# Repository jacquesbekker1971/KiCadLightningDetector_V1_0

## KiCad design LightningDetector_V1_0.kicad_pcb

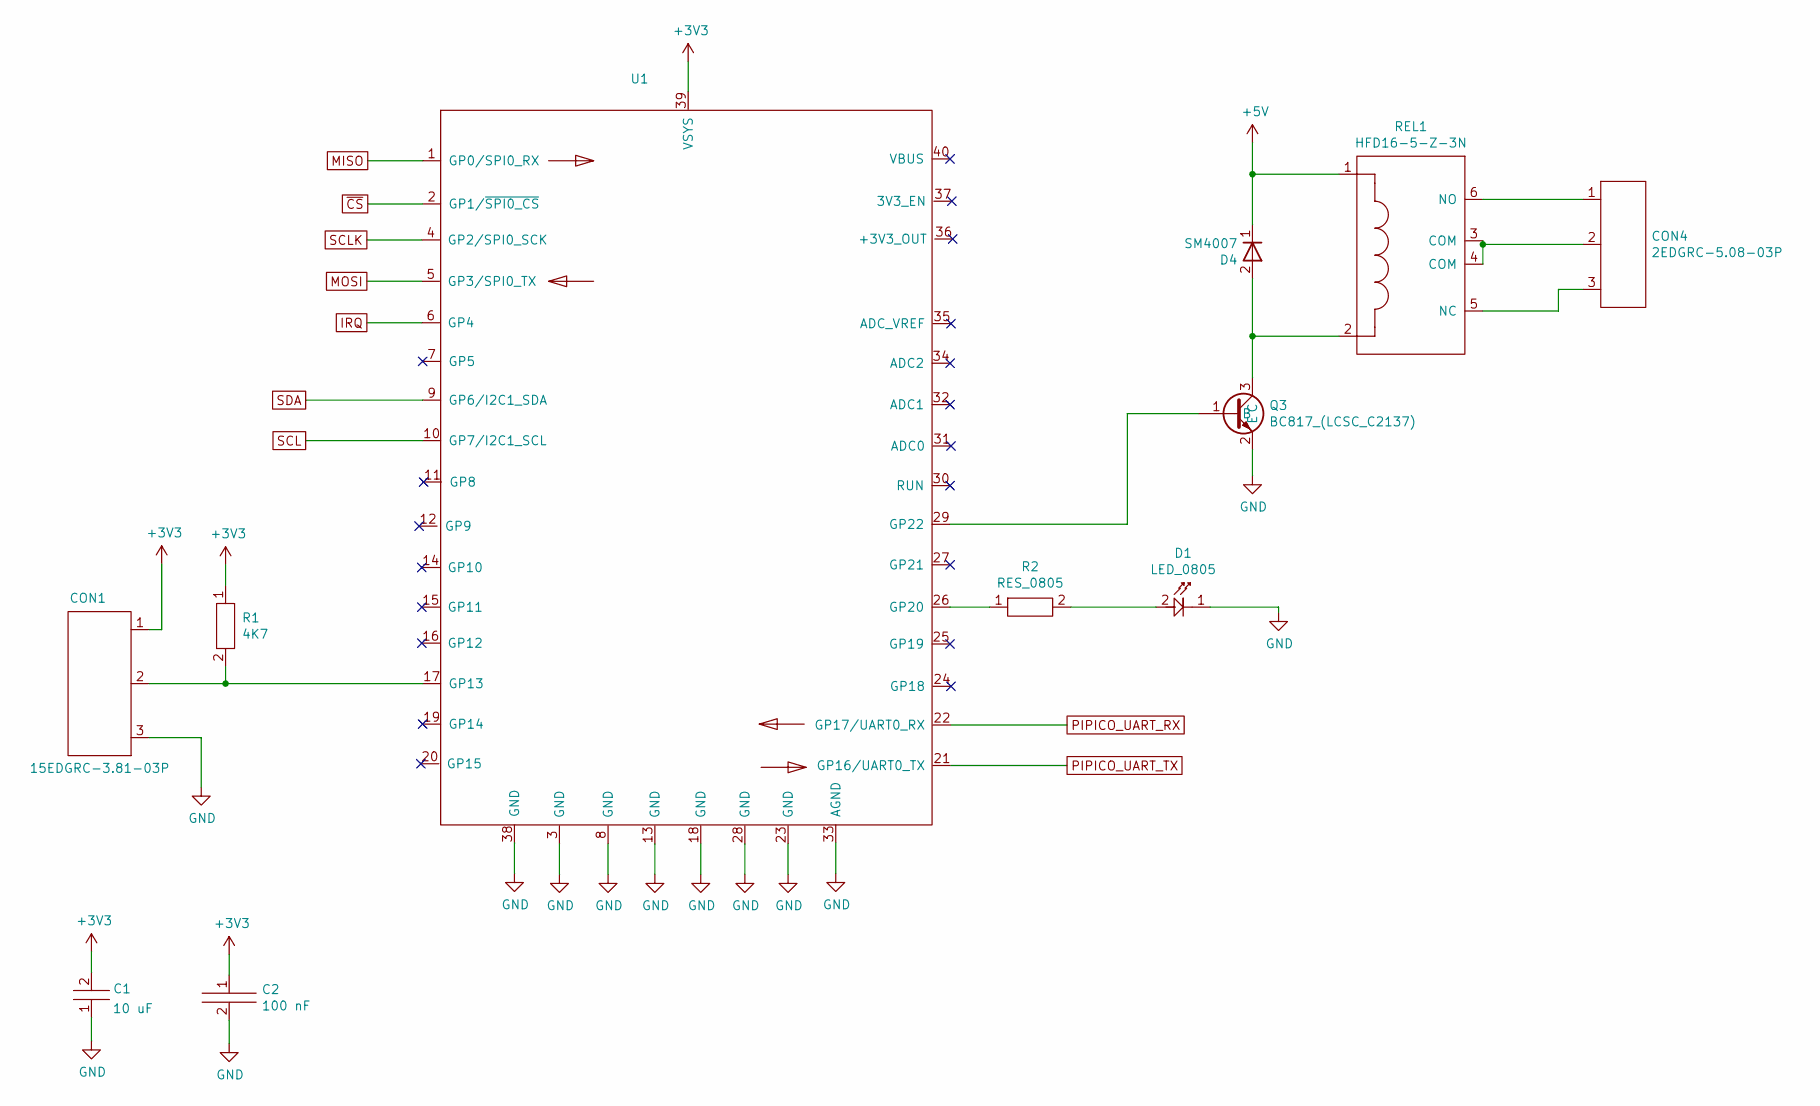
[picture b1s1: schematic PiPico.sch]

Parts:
C1: 10 uF; 1206
C2: 100 nF; C_0805_2012Metric_Pad1.18x1.45mm_HandSolder
CON1: 15EDGRC-3.81-03P
CON4: 2EDGRC-5.08-03P
D1: LED_0805
D4: SM4007; DO-213AB
Q3: BC817_(LCSC_C2137); SOT_23
R1: 4K7; R_0805_2012Metric_Pad1.20x1.40mm_HandSolder
R2: RES_0805; R_0805_2012Metric_Pad1.20x1.40mm_HandSolder
REL1: HFD16-5-Z-3N
U1: PiPico

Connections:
+5V: D4.1, REL1.1; also elsewhere on the board
GND: C1.1, C2.2, CON1.3, D1.1, Q3.2 (E), U1.3 (GND), U1.8 (GND), U1.13 (GND), U1.18 (GND), U1.23 (GND), U1.28 (GND), U1.33 (AGND), U1.38 (GND); also elsewhere on the board
IRQ: U1.6 (GP4); also elsewhere on the board
MISO: U1.1 (GP0/SPI0_RX); also elsewhere on the board
MOSI: U1.5 (GP3/SPI0_TX); also elsewhere on the board
unnamed: CON1.2, R1.2, U1.17 (GP13)
unnamed: CON4.1, REL1.6 (NO)
unnamed: CON4.2, REL1.3 (COM), REL1.4 (COM)
unnamed: CON4.3, REL1.5 (NC)
unnamed: D1.2, R2.2
unnamed: D4.2, Q3.3 (C), REL1.2
unnamed: Q3.1 (B), U1.29 (GP22)
unnamed: R2.1, U1.26 (GP20)
PIPICO_UART_RX: U1.22 (GP17/UART0_RX); also elsewhere on the board
PIPICO_UART_TX: U1.21 (GP16/UART0_TX); also elsewhere on the board
SCL: U1.10 (GP7/I2C1_SCL); also elsewhere on the board
SCLK: U1.4 (GP2/SPI0_SCK); also elsewhere on the board
SDA: U1.9 (GP6/I2C1_SDA); also elsewhere on the board
~CS: U1.2 (GP1/~SPI0_CS); also elsewhere on the board

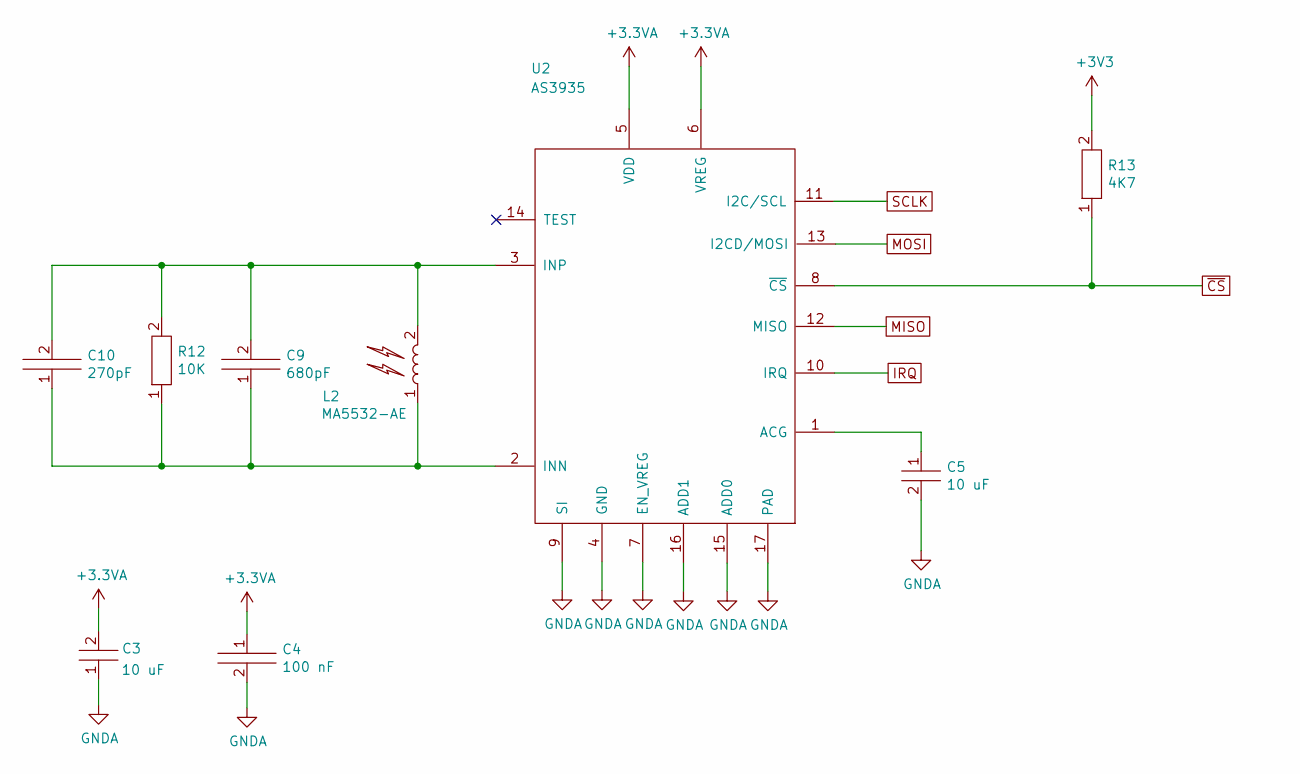
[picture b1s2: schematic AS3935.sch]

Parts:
C3, C5: 10 uF; 1206
C4: 100 nF; C_0805_2012Metric_Pad1.18x1.45mm_HandSolder
C9: 680pF; C_0805_2012Metric_Pad1.18x1.45mm_HandSolder
C10: 270pF; C_0805_2012Metric_Pad1.18x1.45mm_HandSolder
L2: MA5532-AE
R12: 10K; R_0805_2012Metric_Pad1.20x1.40mm_HandSolder
R13: 4K7; R_0805_2012Metric_Pad1.20x1.40mm_HandSolder
U2: AS3935; MLPQ16_4x4

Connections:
+3.3VA: C3.2, C4.1, U2.5 (VDD), U2.6 (VREG); also elsewhere on the board
GNDA: C3.1, C4.2, C5.2, U2.4 (GND), U2.7 (EN_VREG), U2.9 (SI), U2.15 (ADD0), U2.16 (ADD1), U2.17 (PAD); also elsewhere on the board
IRQ: U2.10 (IRQ); also elsewhere on the board
MISO: U2.12 (MISO); also elsewhere on the board
MOSI: U2.13 (I2CD/MOSI); also elsewhere on the board
unnamed: C5.1, U2.1 (ACG)
unnamed: C9.1, C10.1, L2.1, R12.1, U2.2 (INN)
unnamed: C9.2, C10.2, L2.2, R12.2, U2.3 (INP)
SCLK: U2.11 (I2C/SCL); also elsewhere on the board
~CS: R13.1, U2.8 (~CS); also elsewhere on the board

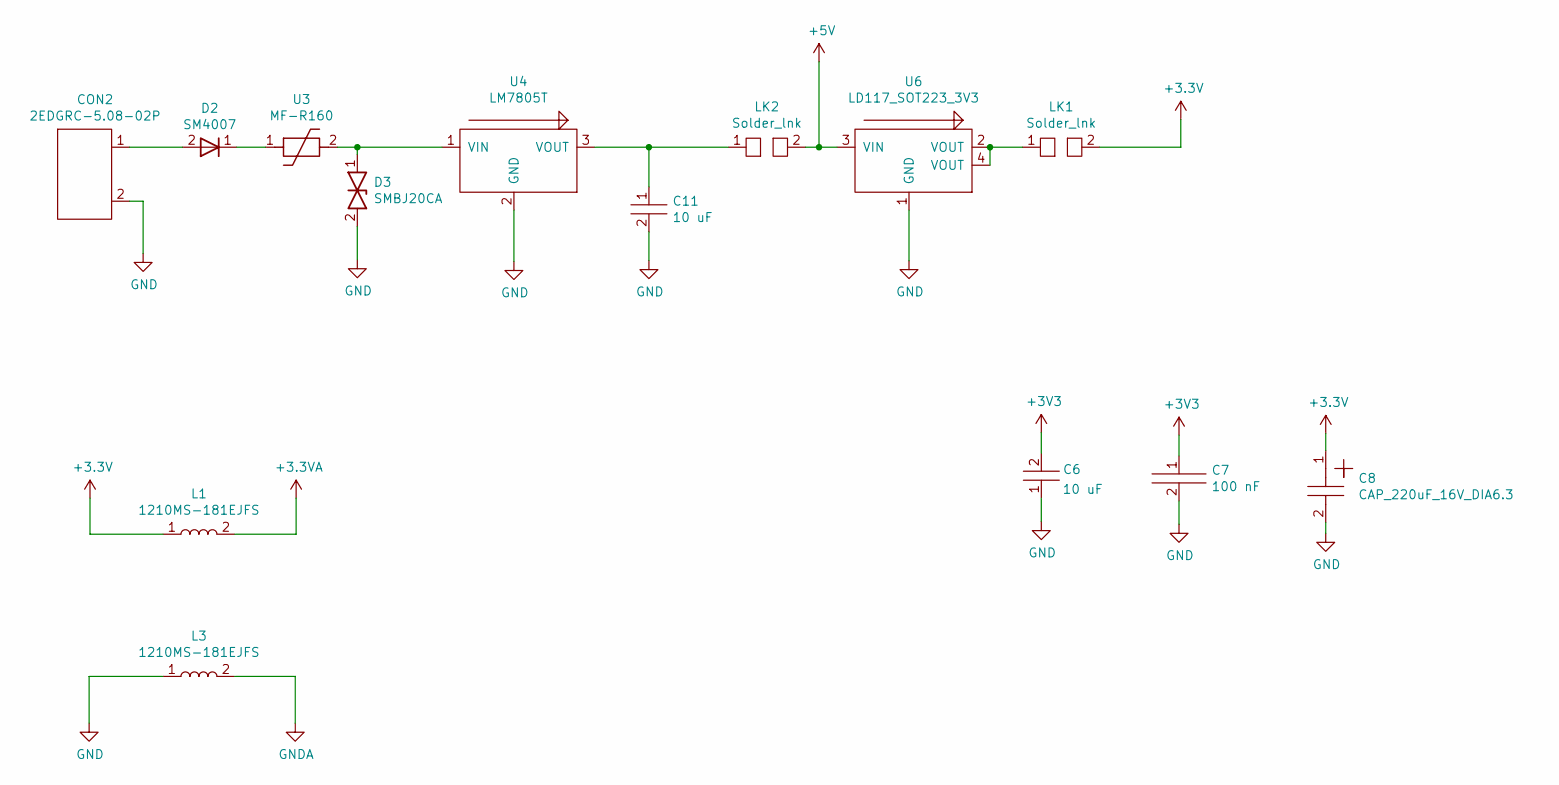
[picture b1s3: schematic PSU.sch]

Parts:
C6, C11: 10 uF; 1206
C7: 100 nF; C_0805_2012Metric_Pad1.18x1.45mm_HandSolder
C8: CAP_220uF_16V_DIA6.3
CON2: 2EDGRC-5.08-02P
D2: SM4007; DO-213AB
D3: SMBJ20CA; DO214AA
L1, L3: 1210MS-181EJFS; 1210
LK1, LK2: Solder_lnk
U3: MF-R160
U4: LM7805T; TO-220-VERT
U6: LD117_SOT223_3V3; SOT_223

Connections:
+3.3VA: L1.2; also elsewhere on the board
+5V: LK2.2, U6.3 (VIN); also elsewhere on the board
GND: C6.1, C7.2, C8.2, C11.2, CON2.2, D3.2, L3.1, U4.2 (GND), U6.1 (GND); also elsewhere on the board
GNDA: L3.2; also elsewhere on the board
unnamed: C11.1, LK2.1, U4.3 (VOUT)
unnamed: CON2.1, D2.2
unnamed: D2.1, U3.1
unnamed: D3.1, U3.2, U4.1 (VIN)
unnamed: LK1.1, U6.2 (VOUT), U6.4 (VOUT)

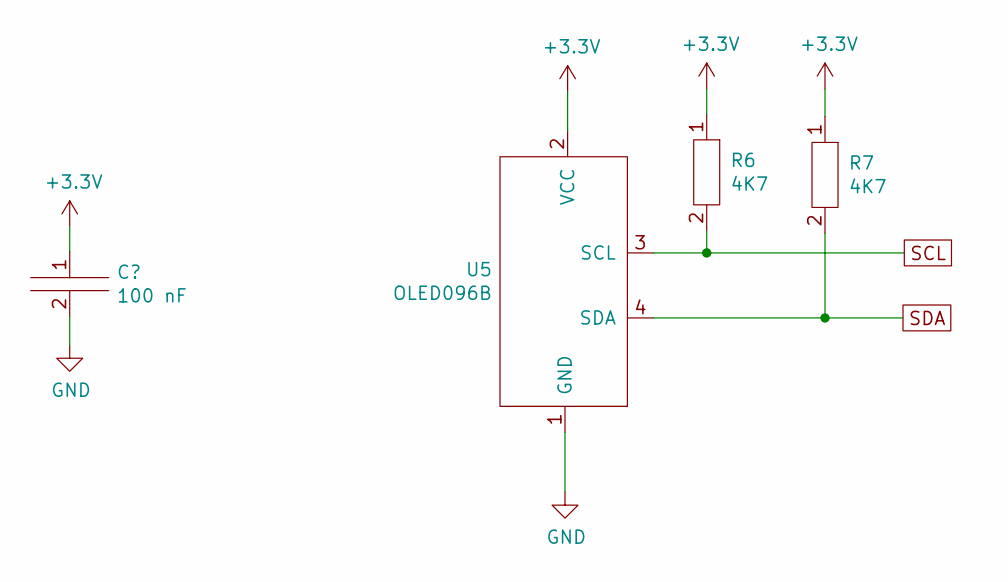
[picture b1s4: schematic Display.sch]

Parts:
R6, R7: 4K7; R_0805_2012Metric_Pad1.20x1.40mm_HandSolder
U5: OLED096B

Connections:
GND: U5.1 (GND); also elsewhere on the board
SCL: R6.2, U5.3 (SCL); also elsewhere on the board
SDA: R7.2, U5.4 (SDA); also elsewhere on the board

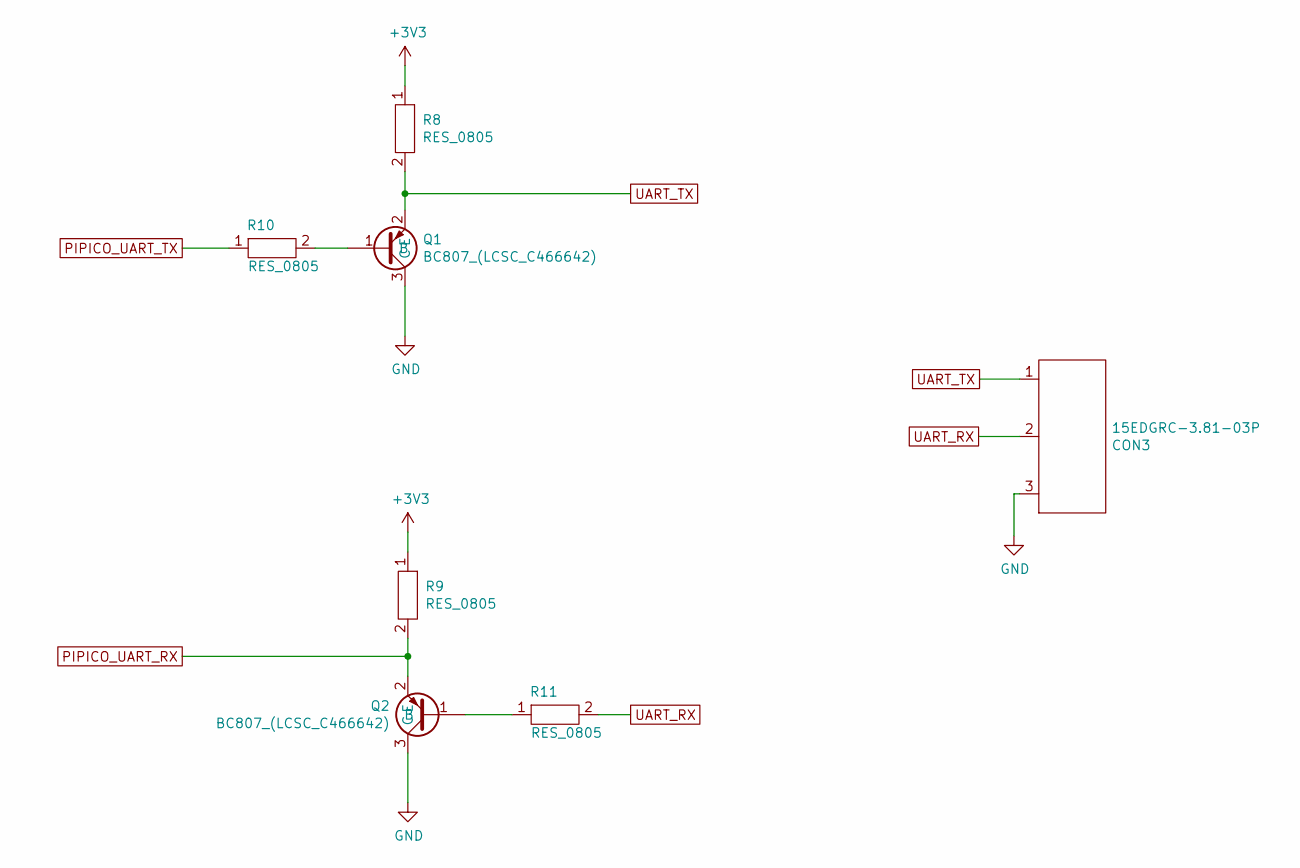
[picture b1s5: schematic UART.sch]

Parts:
CON3: 15EDGRC-3.81-03P
Q1, Q2: BC807_(LCSC_C466642); SOT_23
R8, R9, R10, R11: RES_0805; R_0805_2012Metric_Pad1.20x1.40mm_HandSolder

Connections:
GND: CON3.3, Q1.3 (C), Q2.3 (C); also elsewhere on the board
unnamed: Q1.1 (B), R10.2
unnamed: Q2.1 (B), R11.1
PIPICO_UART_RX: Q2.2 (E), R9.2; also elsewhere on the board
PIPICO_UART_TX: R10.1; also elsewhere on the board
UART_RX: CON3.2, R11.2
UART_TX: CON3.1, Q1.2 (E), R8.2

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
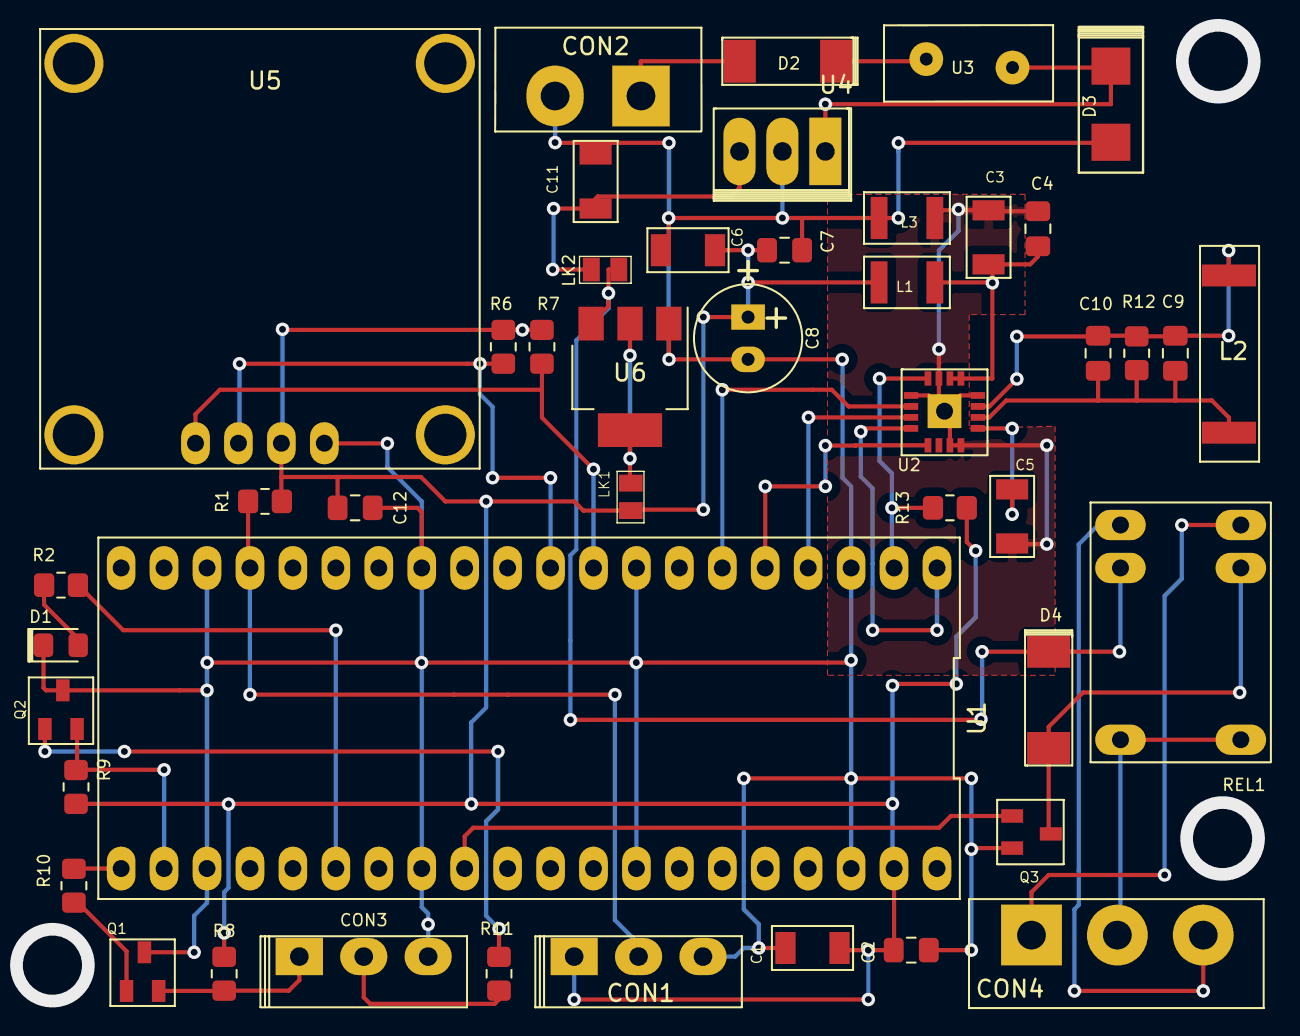
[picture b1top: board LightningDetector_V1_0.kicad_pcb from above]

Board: 2 copper layers, 45 parts (0 on the bottom side), 34 nets.

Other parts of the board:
C12: 100 nF; C_0805_2012Metric_Pad1.18x1.45mm_HandSolder

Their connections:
GND: C12.2; also elsewhere on the board
